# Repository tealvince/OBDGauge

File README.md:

# vOBD: The K-line Super Gauge
By Vince Lee (c)2024-2026

## Description

This project is a custom OBD cluster gauge and experimentation platform for ECUs 
with a k-line interface, driven by an Arduino nano and intended to be installed 
in a 2" diameter circular pod.

## Feature overview

* 25 displayable parameters, including instantaneous and cumulative stats
* Metric/Imperial units
* Ability to hide/show individual gauges
* Built-in readiness monitor reader
* Built-in engine code reader
* Built-in menu to clear engine codes
* Adjustable brightness
* Iso-9140, Kwp-2000 (slow) and Kwp-2009 (fast) interfaces
* Numeric display with color led ring
* Persisting of settings with auto-save on power-off
* Auto-detect and cycling of protocols on startup or disconnect
* Custom circuit board layout

## Supported gauges (functionality is vehicle-dependent)

* Battery voltage level
* Accumulated runtime
* Accumulated distance
* Average fuel efficiency
* Average speed
* G-Force
* Wheel Horsepower
* Gear
* NV Ratio (rpm/speed)
* Speed
* Tachometer
* Coolant temp
* Air intake pressure
* Air intake flow
* Throttle percentage
* Engine load
* Timing advance
* Fuel tank level
* Fuel consumption rate
* Air/Fuel trim
* Air/Fuel equivalence ratio
* O2 a/b sensor voltages

## General usage

* Press button 2 to advance to the next gauge.
* Press button 1 to see the previous gauge.
* Long press button 1 to change brightness
* Long press button 2 to open the settings menu.
* Press button 2 to advance to the next item in settings menu.
* Press button 1 to backup to previous item in settings menu.
* Long press button 2 to select an item in the settings menu.

## Settings menu items

* Back (return to main display)

### History
* Erase all (clear cumulative/average gauges)
* Erase cumulative distance
* Erase cumulative fuel
* Erase cumulative time
* Adjust cumulative distance
* Adjust cumulative fuel
* Adjust cumulative time

### Brighness
* brightness levels 1-5

### Gauges
* Toggle current gauge units (metric/us)
* All gauges to SI Units
* All gauges to US Units
* Hide current gauge
* Show gauge (select from list)
* Auto hide/show gauges based on supported PIDs
* See info (dump raw hex data from current gauge)

### Codes
* Check readiness status
* Read codes
* Clear codes

### Values
* Burn adjustment (set multiplier to fine-tune fuel usage/efficiency stats)
* Vehicle weight adjustment (used to calculate HP)
* Show gear NV ratio thresholds
* Start gear auto-detect drive cycle
* Add gear
* Remove gear
* Edit gear threshold (1-8)

### Modes
* Toggle Loop mode (auto-advance gauges) 
* Toggle Demo mode (simulate ECU reponses)
* Toggle Debug mode (show received bytes)
* Enter Sniff mode (listen to K+ line and show received data; use with Y cable and other device)

## Hardware

* Custom circuit board
* Arduino nano every
* Neopixel 16-LED ring light
* TM1637 4-Digit LED numeric display
* LM2903 Dual comparator IC
* 2N3906 Transistor

## Circuit

To read to and write from the K-Line, a dual comparator chip does the work of converting 
between 5V and 12V logic levels, using voltage dividers to yield 6V and 2.5V reference
voltages.  The output of the "write" comparator goes to a PNP transistor to pull the k-line 
low when sending data back to the PCM, safely sinking more current than the comparator 
can on its own.

To power the arduino, an ignition-switched 12V output is fed to the built-in regulator 
on the Arduino Nano Every (previous iterations used an external voltage regulator with
a plain Arduino Nano, whole upper voltage limit was only 12V).  A large capacitor briefly 
keeps the unit running long enough to save state to persistent memory after the ignition 
is turned off.

## Software

The gauge software is written in C++ with minimal libraries to drive the LED displays.
Serial communication is done with raw bit banging, implementing serial port communication 
purely in software timed off the Arduino microsecond timer.

## Testing

Try out the software or experiment with code changes in a simulated environment using
the following  WOKWI project.  Recommend enabling Demo Mode from the settings menu
since the ECU itself is not simulated:

https://wokwi.com/projects/430523461712229377

## Case

The case and internal spacers and supports are 3D printed.  Stl files are included, as 
well as an svg for the front glass with laser cut holes for the buttons.

Case parts include:

* front glass (laser cut acrylic)
* case body (3d printed)
* case rear (3d printed)
* light mask for led ring (3d printed)
* button extensions (3d printed)
* left and right led digit spacers/supports (3d printed)
* led ring spacer/support (3d printed)

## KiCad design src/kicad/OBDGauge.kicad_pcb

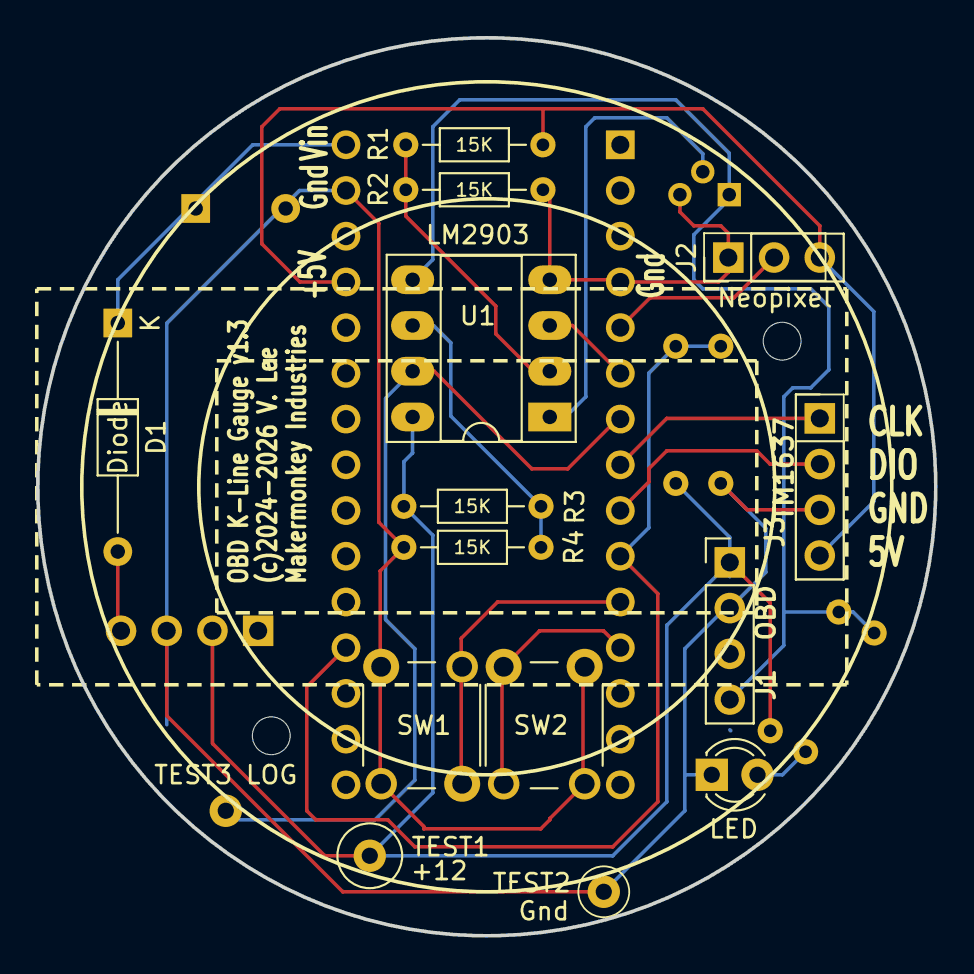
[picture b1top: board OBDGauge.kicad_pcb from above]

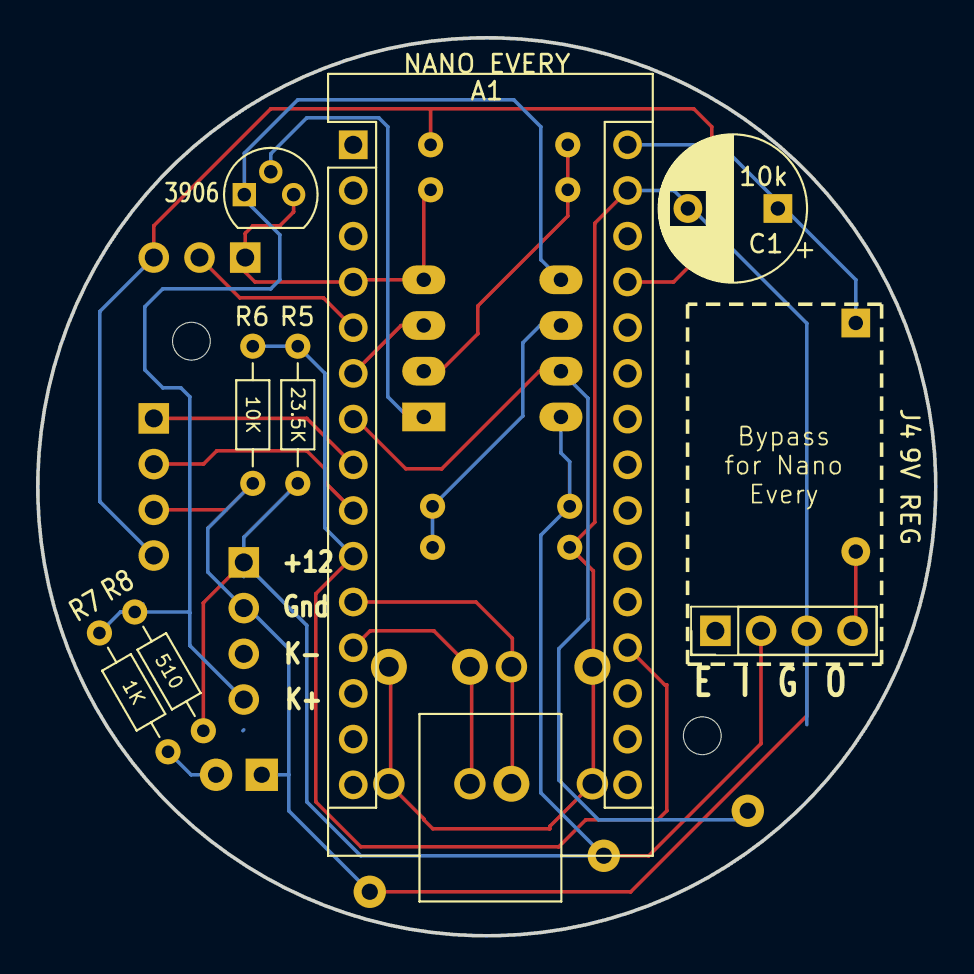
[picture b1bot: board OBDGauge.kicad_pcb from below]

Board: 2 copper layers, 49.9 x 49.9 mm, 25 parts (8 on the bottom side), 18 nets.

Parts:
A1: NANO EVERY; Arduino_Nano
C1: 10000uF; CP_Radial_D8.0mm_P5.00mm
D1: Diode; D_DO-35_SOD27_P12.70mm_Horizontal
D2: LED; LED_D3.0mm
HOLE1, HOLE2: MountingHole_2.1mm
J1: OBD; PinHeader_1x04_P2.54mm_Vertical
J2: Neopixel; PinHeader_1x03_P2.54mm_Vertical
J3: TM1637; PinHeader_1x04_P2.54mm_Vertical
J4: 9V REG; PinHeader_1x04_P2.54mm_Vertical
Q1: 3906; TO-92
R1, R2, R3, R4, R6: 15K; R_Axial_DIN0204_L3.6mm_D1.6mm_P7.62mm_Horizontal
R5: 30K; R_Axial_DIN0204_L3.6mm_D1.6mm_P7.62mm_Horizontal
R7: 1K; R_Axial_DIN0204_L3.6mm_D1.6mm_P7.62mm_Horizontal
R8: 10K; R_Axial_DIN0204_L3.6mm_D1.6mm_P7.62mm_Horizontal
SW1: SW1; SW_PUSH_6mm_H8.5mm
SW2: SW2; SW_PUSH_6mm_H8.5mm
TEST1: +12; TestPoint_Loop_D3.50mm_Drill0.9mm_Beaded
TEST2, TEST3 LOG: GND
U1: LM2903; DIP-8_W7.62mm_Socket_LongPads

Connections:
/5V: A1.27 (+5V), J2.3, J3.4, R1.2
/9V OUT: D1.2 (A), J4.4
/12V: J1.1, J4.2, R3.1, R5.1, R8.2, TEST1.1, U1.8 (V+)
/BATMON: A1.10 (D7), A1.19 (A0), R5.2, R6.2
/DIG-CLK: A1.8 (D5), J3.1
/DIG-DIO: A1.9 (D6), J3.2
/K+: J1.4, Q1.1 (E), R7.1, R8.1, U1.5 (+)
/K-IN: A1.7 (D4), TEST3 LOG.1, U1.7
/K-OUT: A1.6 (D3), U1.3 (+)
/RING: A1.5 (D2), J2.2
/SW1: A1.11 (D8), SW1.2
/SW2: A1.12 (D9), SW2.2
/VSUPPLY: A1.30 (VIN), C1.1, D1.1 (K)
GNDREF: A1.4 (GND), A1.29 (GND), C1.2, D2.1 (K), J1.2, J2.1, J3.3, J4.3, Q1.3 (C), R2.2, R4.1, R6.1, SW1.1, SW2.1, TEST2.1, U1.4 (V-)
unnamed: D2.2 (A), R7.2
unnamed: Q1.2 (B), U1.1
unnamed: R1.1, R2.1, U1.2 (-)
unnamed: R3.2, R4.2, U1.6 (-)

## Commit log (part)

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2024-12-22 Create fp_info_cache
2024-12-22 Create temp
2024-12-22 Create foo
2024-12-22 Create temp2
2024-12-22 Rename src/kicad/temp to src/kicad/temp2/temp
2024-12-25 Update battery level multiplier
2024-12-25 Update battery voltage divider and add k+ pullup
2025-02-05 Update foo
2025-05-11 Add files via upload
    Update files to version 1.2
2025-07-06 Add files via upload
    Fixed shift and mask values
2026-04-20 Added gear, horsepower, and g-force gauges
    * Added gear indicator
    * Added horsepower indicator
    * Added gforce indicator
    * Fixed some bugs with imperial/metric units and persistence
    * Restructured settings into submenus
    * Added settings menus to individually clear cumulative distance/fuel/time counters
2026-04-20 Updated case, angling back to reduce footprint
2026-04-20 Updated to reflect Nano Every
    Updated voltage divider value and note to reflect voltage regulator no longer needed for Nano Every.
2026-04-20 Updates output for Nano Every
2026-06-06 Add files via upload
    Fix mpg calculations

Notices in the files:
src/kicad/OBDGauge.kicad_pcb:
(c)2024-2026 V. Lee
